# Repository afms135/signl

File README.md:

# signl - An Open Source Real-Time Audio Effects Processor running on Raspberry Pi

*signl* is an audio effects processor developed to provide an open-source (modifiable and extendable), real-time (no noticable playing latency), low-cost (Raspberry Pi based) standalone unit for musicians. Development started at the University of Glasgow for ENG5220: Real Time Embedded Programming 2019-2020.

The main features are:

* Mic or Line level in
* Line and Headphone out
* Up to five serial audio effects
* Real time parameter control of each effect
* Easy to understand GUI
* Half rack size

## Video Walkthrough

<p align="center">
  
</p>

## Documentation

See our [Github wiki](https://github.com/afms135/signl/wiki) for detailed instructions on how to reproduce the system, as well as information about the design of the system. Detailed software documentation can be found in the [Doxygen documentation](https://afms135.github.io/signl/).

## Social Media

- [Twitter](https://twitter.com/signlHW)
- [Youtube](https://www.youtube.com/channel/UChTp4nFLsnpuzNy29fdVIeA)

## Authors and Individual Contributions

- Alexander Strachan (afms135, 2173868s) - Software Architect:  wrote hardware/JACK interface code, effect plugin system and two effects (amplifier, overdrive).
- Robert Norris (robnorr, 2198915n) - Software: Wrote GUI code (including tuner), five effects (EQ, Noise Gate, Reverb, Saturation, Vinyl), performed tests and generated data for the wiki. Contributed to the social media promotion.
- Simon Ridley (ithinkitssimon, 2187742r) - Hardware: Designed electronics and mechanical aspects of project, wrote tremolo plugin, documented relevant aspects and contributed to social media of project.

## COVID-19

The project hardware was completed before the 15th of March, so this did not prevent completion of the project, however the full project enclosure could not be manufactured. The designs for this enclosure have been included.

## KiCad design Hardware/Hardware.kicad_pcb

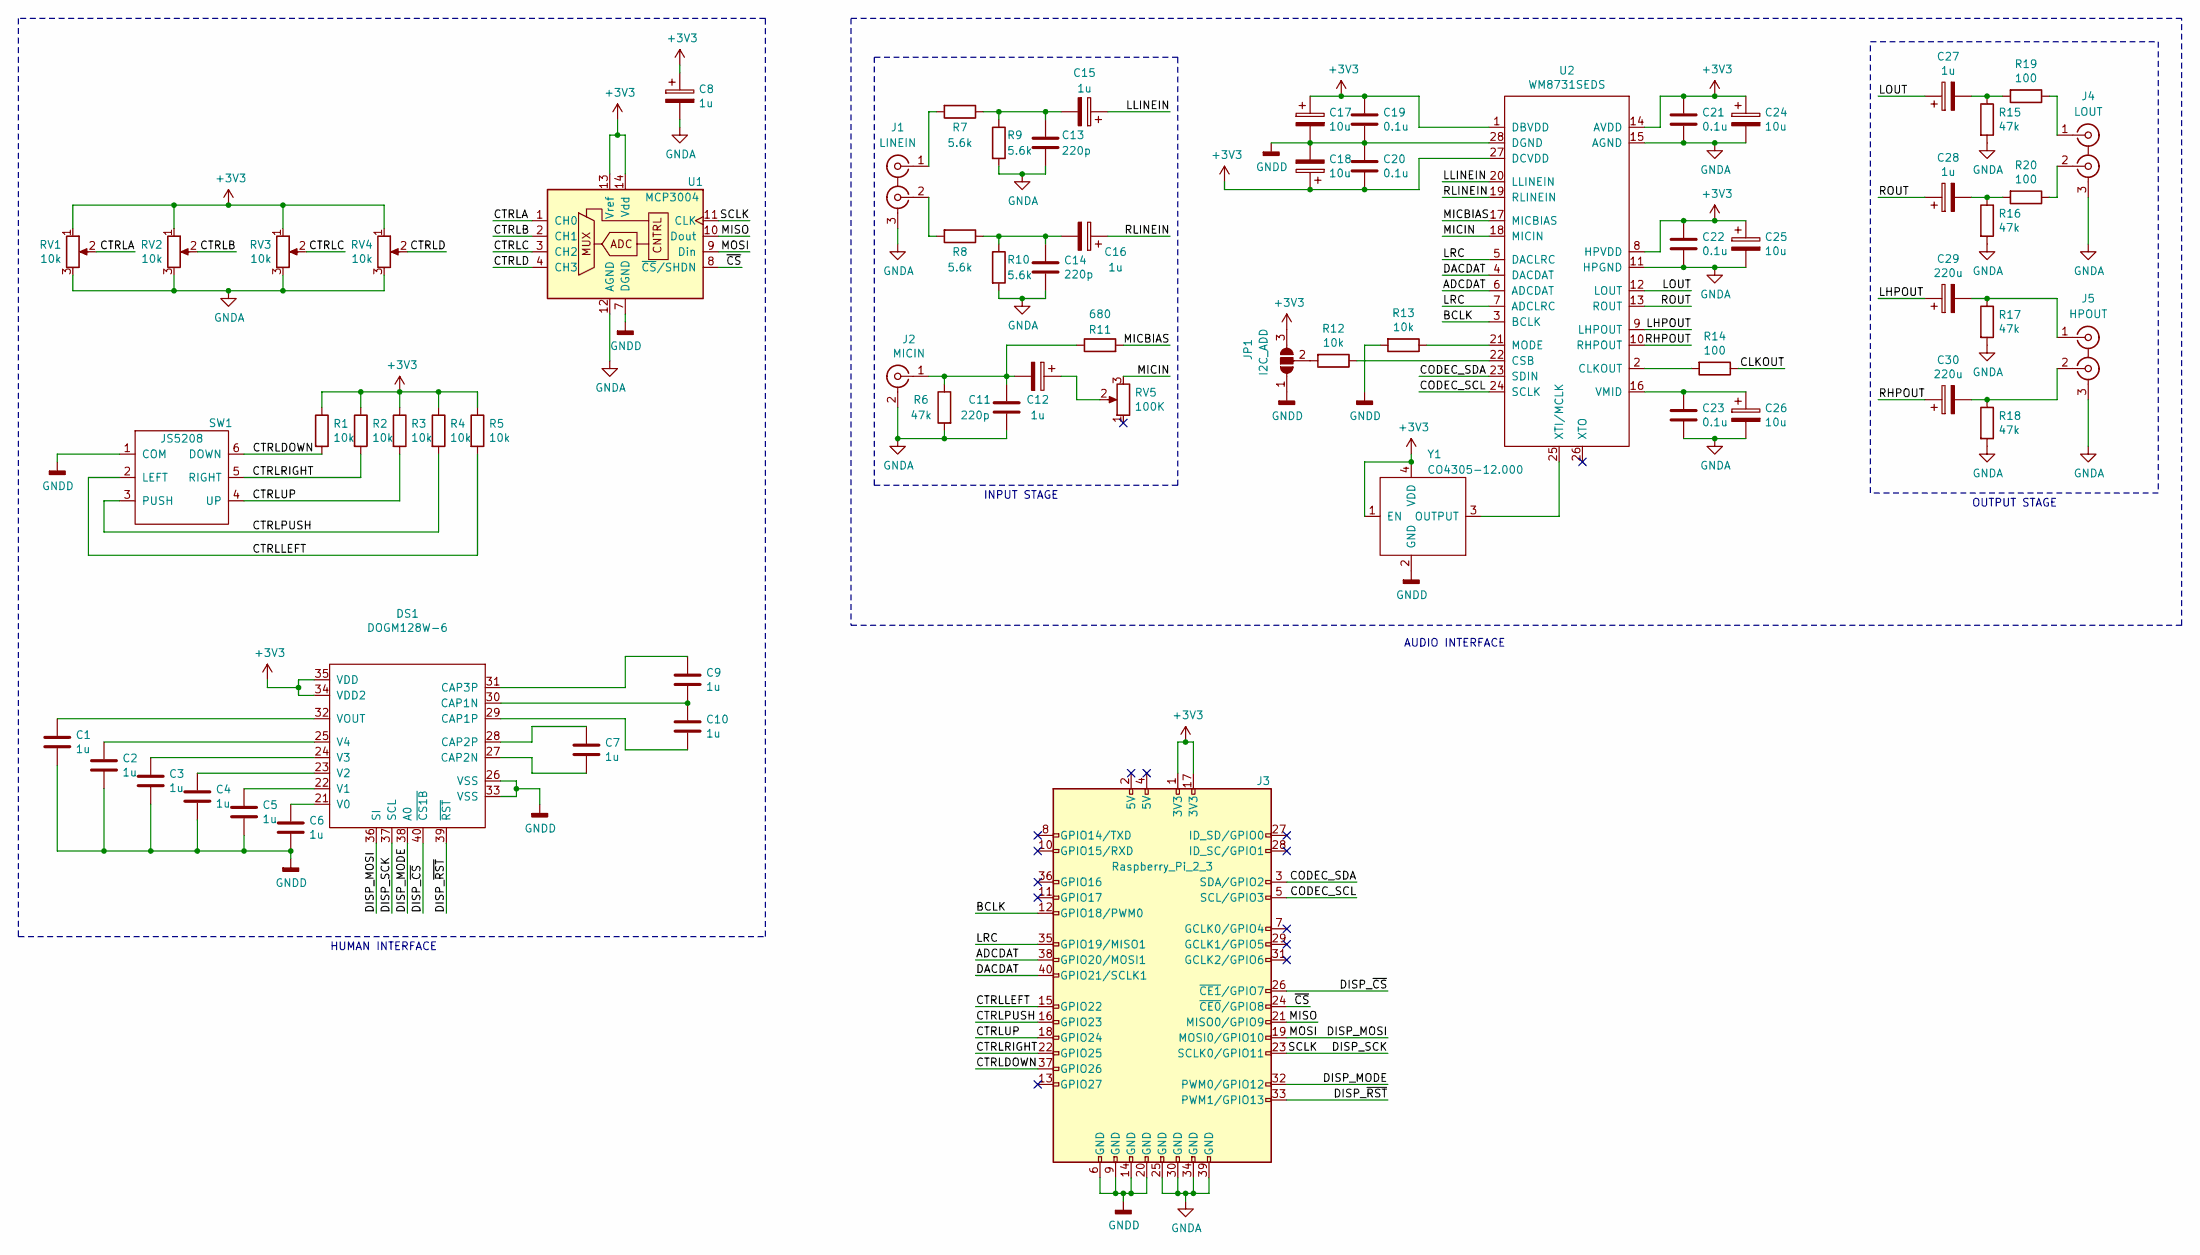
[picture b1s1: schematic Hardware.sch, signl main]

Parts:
C1, C2, C3, C4, C5, C6, C7, C9, C10: 1u; C_0603_1608Metric_Pad1.05x0.95mm_HandSolder
C8, C12, C15, C16, C27, C28: 1u; CP_EIA-3528-12_Kemet-T_Pad1.50x2.35mm_HandSolder
C11, C13, C14: 220p; C_0603_1608Metric_Pad1.05x0.95mm_HandSolder
C17, C18, C24, C25, C26: 10u; CP_EIA-7343-15_Kemet-W_Pad2.25x2.55mm_HandSolder
C19, C20, C21, C22, C23: 0.1u; C_0805_2012Metric_Pad1.15x1.40mm_HandSolder
C29, C30: 220u; CP_Elec_8x10
DS1: DOGM128W-6; DOGM128W
J1: LINEIN; Molex_KK-254_AE-6410-03A_1x03_P2.54mm_Vertical
J2: MICIN; Molex_KK-254_AE-6410-02A_1x02_P2.54mm_Vertical
J3: Raspberry_Pi_2_3; PinHeader_2x20_P2.54mm_Vertical
J4: LOUT; Molex_KK-254_AE-6410-03A_1x03_P2.54mm_Vertical
J5: HPOUT; Molex_KK-254_AE-6410-03A_1x03_P2.54mm_Vertical
JP1: I2C_ADD; SolderJumper-3_P1.3mm_Open_RoundedPad1.0x1.5mm_NumberLabels
R1, R2, R3, R4, R5, R12, R13: 10k; R_0805_2012Metric_Pad1.15x1.40mm_HandSolder
R6, R15, R16, R17, R18: 47k; R_0805_2012Metric_Pad1.15x1.40mm_HandSolder
R7, R8, R9, R10: 5.6k; R_0805_2012Metric_Pad1.15x1.40mm_HandSolder
R11: 680; R_0805_2012Metric_Pad1.15x1.40mm_HandSolder
R14, R19, R20: 100; R_0805_2012Metric_Pad1.15x1.40mm_HandSolder
RV1, RV2, RV3, RV4: 10k; Molex_KK-254_AE-6410-03A_1x03_P2.54mm_Vertical
RV5: 100K; Molex_KK-254_AE-6410-03A_1x03_P2.54mm_Vertical
SW1: JS5208
U1: MCP3004; SOIC-14_3.9x8.7mm_P1.27mm
U2: WM8731SEDS; SSOP-28_5.3x10.2mm_P0.65mm
Y1: CO4305-12.000

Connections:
+3V3: C8.1, C17.1, C18.1, C19.1, C20.2, C21.1, C22.1, C24.1, C25.1, DS1.34 (VDD2), DS1.35 (VDD), J3.1 (3V3), J3.17 (3V3), JP1.3 (B), R1.1, R2.1, R3.1, R4.1, R5.1, RV1.1, RV2.1, RV3.1, RV4.1, U1.13 (Vref), U1.14 (Vdd), U2.1 (DBVDD), U2.8 (HPVDD), U2.14 (AVDD), U2.27 (DCVDD), Y1.1 (EN), Y1.4 (VDD)
/ADCDAT: J3.38 (GPIO20/MOSI1), U2.6 (ADCDAT)
/BCLK: J3.12 (GPIO18/PWM0), U2.3 (BCLK)
/CLKOUT: R14.1
/CODEC_SCL: J3.5 (SCL/GPIO3), U2.24 (SCLK)
/CODEC_SDA: J3.3 (SDA/GPIO2), U2.23 (SDIN)
/CTRLA: RV1.2, U1.1 (CH0)
/CTRLB: RV2.2, U1.2 (CH1)
/CTRLC: RV3.2, U1.3 (CH2)
/CTRLD: RV4.2, U1.4 (CH3)
/CTRLDOWN: J3.37 (GPIO26), R1.2, SW1.6 (DOWN)
/CTRLLEFT: J3.15 (GPIO22), R5.2, SW1.2 (LEFT)
/CTRLPUSH: J3.16 (GPIO23), R4.2, SW1.3 (PUSH)
/CTRLRIGHT: J3.22 (GPIO25), R2.2, SW1.5 (RIGHT)
/CTRLUP: J3.18 (GPIO24), R3.2, SW1.4 (UP)
/DACDAT: J3.40 (GPIO21/SCLK1), U2.4 (DACDAT)
/DISP_MODE: DS1.38 (A0), J3.32 (PWM0/GPIO12)
/DISP_MOSI: DS1.36 (SI), J3.19 (MOSI0/GPIO10), U1.9 (Din)
/DISP_SCK: DS1.37 (SCL), J3.23 (SCLK0/GPIO11), U1.11 (CLK)
/DISP_~CS~: DS1.40 (~CS1B~), J3.26 (~CE1~/GPIO7)
/DISP_~RST~: DS1.39 (~RST~), J3.33 (PWM1/GPIO13)
/LHPOUT: C29.1, U2.9 (LHPOUT)
/LLINEIN: C15.1, U2.20 (LLINEIN)
/LOUT: C27.1, U2.12 (LOUT)
/LRC: J3.35 (GPIO19/MISO1), U2.5 (DACLRC), U2.7 (ADCLRC)
/MICBIAS: R11.2, U2.17 (MICBIAS)
/MICIN: RV5.3, U2.18 (MICIN)
/MISO: J3.21 (MISO0/GPIO9), U1.10 (Dout)
/RHPOUT: C30.1, U2.10 (RHPOUT)
/RLINEIN: C16.1, U2.19 (RLINEIN)
/ROUT: C28.1, U2.13 (ROUT)
/~CS~: J3.24 (~CE0~/GPIO8), U1.8 (~CS~/SHDN)
GNDA: C8.2, C11.2, C13.2, C14.2, C21.2, C22.2, C23.2, C24.2, C25.2, C26.2, J1.3 (EXT), J2.2 (Ext), J3.25 (GND), J3.30 (GND), J3.34 (GND), J3.39 (GND), J4.3 (EXT), J5.3 (EXT), R6.2, R9.2, R10.2, R15.2, R16.2, R17.2, R18.2, RV1.3, RV2.3, RV3.3, RV4.3, U1.12 (AGND), U2.11 (HPGND), U2.15 (AGND)
GNDD: C1.2, C2.2, C3.2, C4.2, C5.2, C6.2, C17.2, C18.2, C19.2, C20.1, DS1.26 (VSS), DS1.33 (VSS), J3.6 (GND), J3.9 (GND), J3.14 (GND), J3.20 (GND), JP1.1 (A), R13.2, SW1.1 (COM), U1.7 (DGND), U2.28 (DGND), Y1.2 (GND)
unnamed: C1.1, DS1.32 (VOUT)
unnamed: C2.1, DS1.25 (V4)
unnamed: C3.1, DS1.24 (V3)
unnamed: C4.1, DS1.23 (V2)
unnamed: C5.1, DS1.22 (V1)
unnamed: C6.1, DS1.21 (V0)
unnamed: C7.1, DS1.28 (CAP2P)
unnamed: C7.2, DS1.27 (CAP2N)
unnamed: C9.1, DS1.31 (CAP3P)
unnamed: C9.2, C10.1, DS1.30 (CAP1N)
unnamed: C10.2, DS1.29 (CAP1P)
unnamed: C11.1, C12.2, J2.1 (In), R6.1, R11.1
unnamed: C12.1, RV5.2
unnamed: C13.1, C15.2, R7.1, R9.1
unnamed: C14.1, C16.2, R8.1, R10.1
unnamed: C23.1, C26.1, U2.16 (VMID)
unnamed: C27.2, R15.1, R19.2
unnamed: C28.2, R16.1, R20.2
unnamed: C29.2, J5.1 (IN1), R17.1
unnamed: C30.2, J5.2 (IN2), R18.1
unnamed: DS1.1 (A1), DS1.2 (A2), DS1.3 (A3), DS1.18 (C1), DS1.19 (C2), DS1.20 (C3)
unnamed: J1.1 (IN1), R7.2
unnamed: J1.2 (IN2), R8.2
unnamed: J4.1 (IN1), R19.1
unnamed: J4.2 (IN2), R20.1
unnamed: JP1.2 (C), R12.2
unnamed: R12.1, U2.22 (CSB)
unnamed: R13.1, U2.21 (MODE)
unnamed: R14.2, U2.2 (CLKOUT)
unnamed: U2.25 (XTI/MCLK), Y1.3 (OUTPUT)

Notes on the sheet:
OUTPUT STAGE
INPUT STAGE
HUMAN INTERFACE
AUDIO INTERFACE

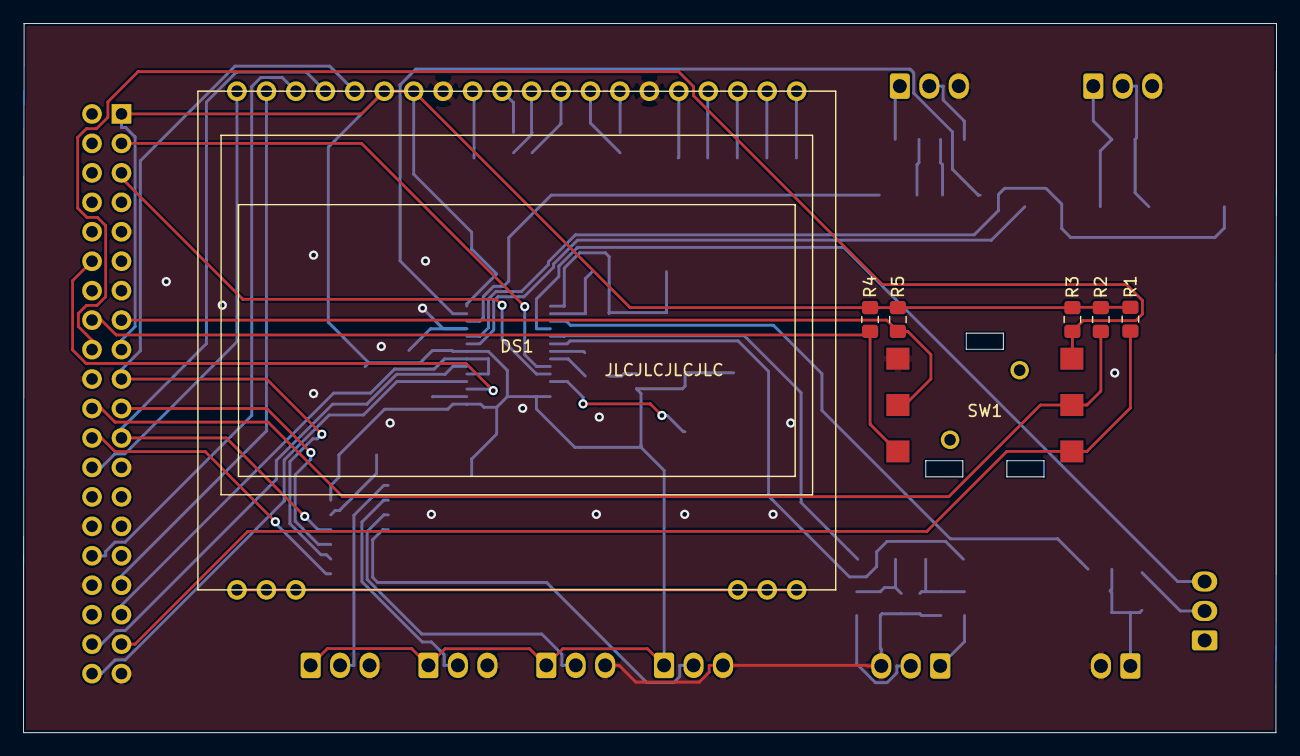
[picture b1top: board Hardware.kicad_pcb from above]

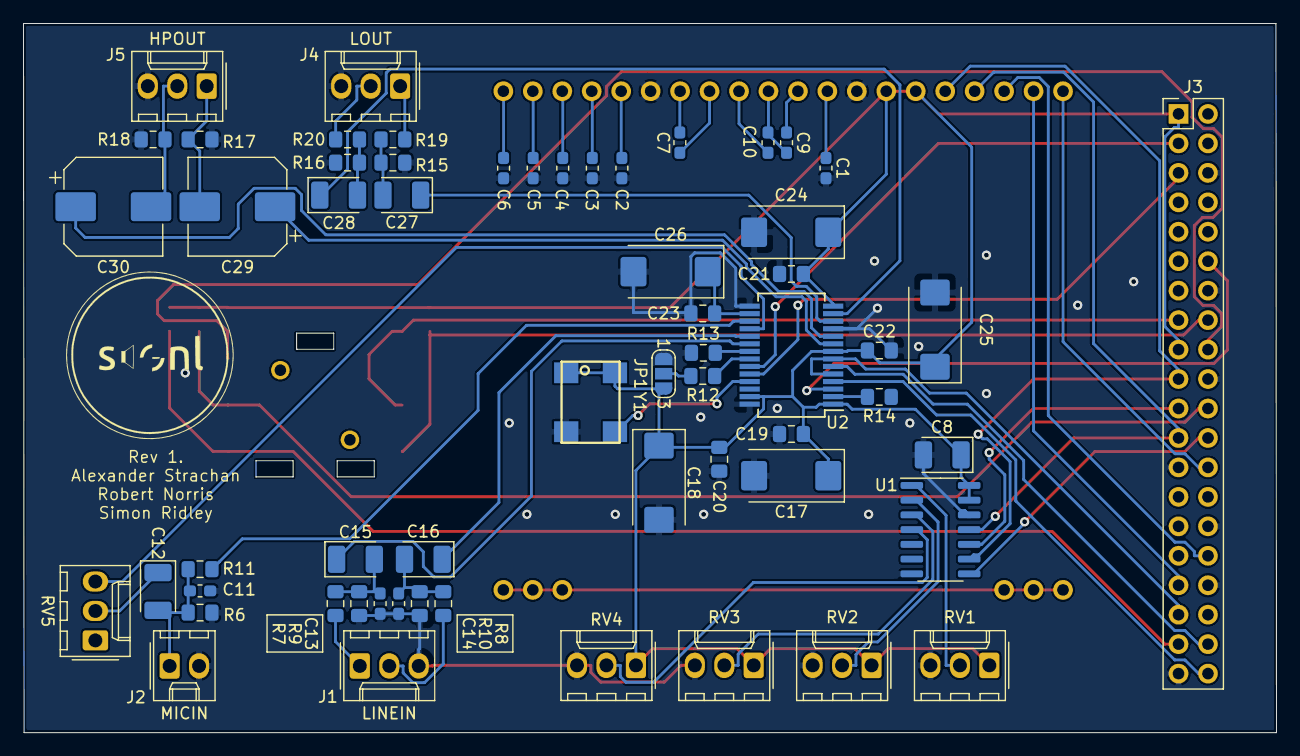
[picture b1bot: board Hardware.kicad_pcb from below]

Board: 2 copper layers, 108.0 x 61.2 mm, 66 parts (59 on the bottom side), 63 nets.

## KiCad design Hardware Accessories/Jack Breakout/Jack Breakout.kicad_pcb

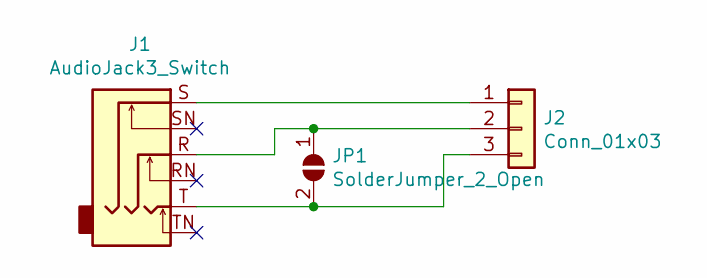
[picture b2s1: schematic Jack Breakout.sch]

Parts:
J1: AudioJack3_Switch; Jack_3.5mm_Neutrik_NMJ6HCD2_Horizontal
J2: Conn_01x03; Molex_KK-254_AE-6410-03A_1x03_P2.54mm_Vertical
JP1: SolderJumper_2_Open; SolderJumper-2_P1.3mm_Open_RoundedPad1.0x1.5mm

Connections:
unnamed: J1.R, J2.2, JP1.1 (A)
unnamed: J1.S, J2.1
unnamed: J1.T, J2.3, JP1.2 (B)

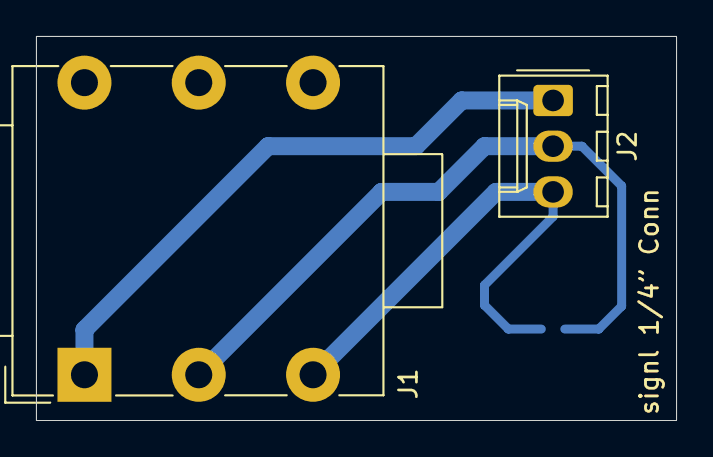
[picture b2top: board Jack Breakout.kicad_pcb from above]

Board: 2 copper layers, 35.6 x 21.3 mm, 3 parts (1 on the bottom side), 3 nets.

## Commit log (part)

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2020-01-29 Initial commit of readme.
2020-02-08 Initial commit of software.
2020-02-08 Add main application class.
2020-02-12 Added schematic symbol for JS5208 Joystick
2020-02-12 Added schematic symbol for WM8731SEDS
2020-02-12 Added footprint for DOGM128W-6 LCD Screen
2020-02-12 Added arrow.
2020-02-12 removed wrongly named folder. Added .DS_Store to gitignore.
2020-02-12 Started schematic, added RPi, Joystick and ControlADC
2020-02-17 Connected WM8731SEDS audio codec to Raspberry Pi through I2S
2020-02-17 Added DOGM128W-6 LCD Screen to schematic with supporting circutiry, corrected error in DOGM128W-6 Schematic part
2020-02-18 Connected WM8731SEDS control interface through i2c to Raspberry Pi, finished connection of all systems
2020-02-19 Assigned PCB footprints to schematic symbols
2020-02-19 Exported schematic sheet as PDF
2020-02-19 Add effect base class.
2020-02-19 Add null effect.
2020-02-19 Started jack breakout CAD.
2020-02-19 Added .ipynb_checkpoints to .gitignore; finished 1/4" jack connector pending review; started exploratory physical design .ipynb
2020-02-22 Split activation of JACK client into seperate function.
2020-02-25 Fixed jack breakout misalignment
2020-02-25 Cleaned up tracks on Jack Breakout
2020-02-25 Routed main PCB
2020-02-25 Cleaned up traces, organised silkscreen, stitched ground planes.
2020-02-25 Added 3D models for components.
2020-02-25 Moved I2C lines, added mounting holes, took renders.
2020-02-26 Add amplifier effect.
2020-02-26 Add configurable parameters to effects.
2020-02-27 Add returnable parameter names to effects.
2020-02-27 Add GPIO output class.
2020-02-27 Add SPI device class.
2020-02-27 initialize display in main application.
2020-02-27 Creates sprites.h file.
2020-02-27 Created .step file of PCB.
2020-02-27 Added .step file for JS5208 Joystick
2020-02-27 Fixed compatability of .step file.
2020-02-28 Add GPIO input class.
2020-02-28 Remove unused main application class destructor.
2020-02-28 Created sprites.cpp to display sprites from sprites.h
2020-02-29 Add input debounce class.
2020-02-29 Use EXIT_* return defines.
2020-02-29 Add ADC driver class.
2020-02-29 Add effect manager class, add to main application.
2020-02-29 Move null effect to effect.h.
2020-02-29 Remove header include guards.
2020-02-29 Rename effect files from .h to .cpp files.
2020-02-29 Add create and destroy functions to plugins.
2020-02-29 Add plugin create/destroy function typedefs.
2020-02-29 Add putpixel() method to LCD class.
2020-03-02 Fix whitespace (spaces to tabs).
2020-03-02 Added clearances for parts, adjusted some dimensions
2020-03-02 Designed box to be 3D printed and attach to Faceplate, will enclose raspberry pi and signl electronics.
2020-03-02 Remove amp and overdrive effects from effect manager class.
2020-03-02 Started main gui screen
2020-03-03 Fix plugin makefile from building ELF binaries instead of SO libraries.
2020-03-03 Search for so plugin files in effect directory.
2020-03-03 Modify effect unique_ptr to use custom deleter.
2020-03-03 Add loaded plugins to effect manager.
2020-03-03 Add move constructor and move assignment operator for effect manager.
2020-03-04 Add travis continuous integration.
2020-03-04 Fix zero initilization of spi_ioc_transfer struct.
2020-03-04 Updated gui class to inherit from lcd class
2020-03-04 Removed sprites.cpp
2020-03-04 Fixed Sprite designated initialisers.
2020-03-04 Fixed effect_chain in gui.h.
2020-03-05 Use initilizer list to set default amp effect gain.
2020-03-05 Add icon definitions to effects.
2020-03-05 Print list of loaded plugins on startup.
2020-03-05 Modify gui::putchar() to use character literals.
2020-03-05 Add option to build effects from main makefile.
2020-03-06 Added saturation effect.
2020-03-06 Fixed last two commits.
2020-03-06 Added drive parameter to saturation effect.
2020-03-06 Moves plugin icons to an array 'icons'.
2020-03-06 Getting plugin icons properly for display.
2020-03-06 Modified Faceplate design to accomodate panelmount components better, Exported .DXFs
2020-03-08 Created noise gate effect.
2020-03-08 Updated saturation effect name and icon.
2020-03-08 Updated tape saturation's gui_icon.
2020-03-09 Use gui class inplace of lcd class.
2020-03-09 Fix req_gpio() always requesting an input pin.
2020-03-10 Designed Faceplate graphics to be printed on viynl.
2020-03-11 Designed Faceplate graphics, with colours inverted and .pdf included for portability.
2020-03-11 Added parameter printing.
2020-03-17 Made schematic symbol for CO4305-12.000 External Oscillator.
2020-03-17 Designed PCB footprint for CO4305-12.000 External Oscillator.
2020-03-19 Add clang to travis CI build.
2020-03-19 Whitespace fixes, surpresing misleading indentaion warning.
2020-03-19 Mark noise gate internal functions as private.
2020-03-19 Use floating point abs() function.
2020-03-19 Started EQ effect.
2020-03-20 Return unsigned int from effect manager, fixes sign comparison warning.
2020-03-20 Pass sample rate to plugin creation function.
2020-03-20 Remove hard coded sample rate from noise gate plugin.
2020-03-20 Ensure plugins are rebuild when effect.h is modified.
2020-03-20 Limited parameter length to 8 characters.
2020-03-20 Added paramval to all effects, which returns the value (between 0. and 1.) of each effect's parameters.
2020-03-20 Added live parameter bars to the gui.
2020-03-21 Updated parameters to be no more than 8 characters.
2020-03-23 Updated saturation effect - new waveshaper and added level and gain parameters. Also rename.
2020-03-23 Updated noise gate parameters.
2020-03-23 Fixed '9' in font.h
2020-03-24 Added -+= to gui::putchar.
2020-03-25 Fixed placement of bars on level_adj screen.
2020-03-27 Add documentation for gpio.h.
2020-03-27 Fixed placement of level bars.
2020-03-28 Move sprite definitions from h to cpp files.
2020-03-28 Rename gui folder to assets.
2020-03-28 Move gui.cpp and gui.h to software root.
2020-03-29 Improve Makefiles.
2020-03-29 Use std::abs() inplace of fabs().
2020-03-29 Fixup header includes.
2020-03-29 Use NUM_EFFECTS constant inplace of numbers.
2020-03-29 Fix documentation punctuation in gpio.h and debounce.h.
2020-03-29 Add private member documentation to gpio.h and debounce.h.
2020-03-29 Add help output to makefile.
2020-03-29 Add documentation for adc class.
2020-03-31 Add documentation for lcd class.
2020-03-31 Added gain boosting up to 12dB for each eq param.
2020-04-01 The all target needs to be first in the Makefile.
2020-04-01 Use 2nd order filter in eq.cpp low and high pass filters.
2020-04-01 Updates initial params of saturation.
2020-04-02 Added a thread to handle the convolution processing.
2020-04-03 Added the convolve function, but it doesn't seem to be affecting the output in any way.
2020-04-03 Converted to sending audio buffers from jack to each plugin.
2020-04-03 Added FFTConvolver submodule to achieve real time convolution without clicks (partitioned convolution).
2020-04-05 Add documentation for spi class.
2020-04-05 Add documentation for Sprite struct.
2020-04-05 Use doxygen to build code documentation, add docs target to Makefile.
2020-04-08 Added more IRs.
2020-04-08 Updated IRs to const floats.
2020-04-08 Added all 6 reverb types to plugin.
2020-04-08 Fixed ir_hall and updated its convolver.
2020-04-08 Stopped clicking in ir_hall.
2020-04-08 Removed the opera and church mode in reverb - it was causing too many problems w/ clicks and glitches.
2020-04-08 Started the vinyl plugin.
2020-04-08 Added vinyl params.
2020-04-08 Added clicks and pops (scratches).
2020-04-08 Move FFTConvolver submodule into effects directory.
2020-04-08 Compile FFTConvolver into reverb plugin.
2020-04-09 Fix trailing whitespace in jack.cpp.
2020-04-09 Started tremolo effect.
2020-04-09 Tried to add filter.
2020-04-09 Fixed tremolo to start making noise again.
2020-04-09 Updated initial period value.
2020-04-09 Added fade option, changed icon.
2020-04-09 Restructured code, fixed fade.
2020-04-09 Added level option.
2020-04-09 Started Media folder and added the signl logo.
2020-04-09 Added YouTube channel link.
2020-04-09 Neatened filter.
2020-04-10 Add documentation for the effect base class.
2020-04-10 Remove unused rate variable from eq plugin.
2020-04-10 Finished vinyl effect, adding the filter and dry-wet parameters.
2020-04-11 Add documentation for effect_manager class.
2020-04-11 Add documentation for null effect.
2020-04-11 Build software in script.
2020-04-11 Enable WM8731 sound card.
2020-04-11 Fix root detection in script.
2020-04-11 Add coloured output to script.
2020-04-11 Install needed prerequisites.
2020-04-11 Enable spidev.
2020-04-11 Check if script it being run as root.
2020-04-11 First pages commit.
2020-04-11 Move definition of NUM_EFFECTS to header file.
2020-04-11 Added eq graph for wiki
2020-04-13 Fix disabling of built in audio card.
2020-04-13 Simplify signl::process() logic, move globals to class.
2020-04-13 Simplify ui display loop.
2020-04-13 Fix gui::putrect documentation.
2020-04-13 Add software overview diagram.
2020-04-13 Move BUFFER_LENGTH and NUM_EFFECTS constants to gui and signl class respectively.
2020-04-13 Simplify parameter setting.
2020-04-13 Update documentation.
2020-04-13 Fixed parameter update bug which only allowed Param A of effect 1, Param B of effect 2 etc... to be updated.
2020-04-13 Added photos for user guide.
2020-04-13 Added EQ equation for wiki.
2020-04-13 In level view, limited the bars to the max height displayed, and added a fixed size rect above any bar which is clipping (going above 0dB).
2020-04-13 Added another photo for the user guide, showing a clipping level bar.
2020-04-14 Add list() function to effect_manager.
2020-04-14 Add effect list class.
2020-04-14 Use effect_manager::list() when printing plugins at start.
2020-04-14 Do not delete effect when they are switched out.
2020-04-14 Use post increment/decrement operators.
2020-04-14 Swapped up and down joystick effect.
2020-04-14 Add effect chain diagram.
2020-04-14 Added test data for EQ plugin.
2020-04-14 Reprocessed the EQ test data.
2020-04-14 Added gnuplot commands file for EQ test data.
2020-04-14 Added Reverb test data.
2020-04-14 Added testing data for Tremolo effect.
2020-04-14 Converted Reverb test .svg files to .png files for lower size.
2020-04-14 Added gridlines to Tremolo test data plot,
2020-04-15 Added Noise Gate test data.
2020-04-15 Generated bill of materials to aid reproducability.
2020-04-15 Added hardware block diagram.
2020-04-16 Added video thumbnail.
2020-04-16 Added video walkthrough link to README
2020-04-17 Added Overdrive testing data.
2020-04-17 Added photo for Wiki.
2020-04-17 Assigned datasheets and supplier links to all schematic components. Regenerated BoM.
2020-04-17 Updated blockdiagram to reflect system.
2020-04-18 Added '#', 'b' and '/' to the font.
2020-04-18 Added new display state for the tuner.
2020-04-18 Add individual contribution for afms135.
2020-04-18 Finished tuner but it's not very accurate because any TUNER_BUFFER_SIZE above 32768 causes a seg fault.
2020-04-18 Exported model for box in numerous formats for most compatibility.
2020-04-18 Modified covid-19 response, added individual contribution.
2020-04-18 Fixed tuner array not being used.
2020-04-18 Added images of realPCB and assembly.
2020-04-18 Tried Gaussian interpolation for the tuner.
2020-04-18 Changes width of gaussian function to increase accuracy.
2020-04-19 Fixed tuner window equation.
2020-04-19 Added photos of the Tuner for the user guide.
2020-04-19 Updated the video walkthrough thumbnal on the README
2020-04-19 Exclude build artefacts in submodules from git.
2020-04-19 Update documentation pages.
